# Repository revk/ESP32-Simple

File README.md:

# Simplest code and PCB for ESP32 projects

The code is the simplest build from RevK library, and as such is an ideal base install from which you can OTA any other code. Can also be used as a staged OTA using "otaurl" in the "OTA" namespace in NVS as an automatic OTA when started.

Copyright © 2019-21 Adrian Kennard, Andrews & Arnold Ltd. See LICENCE file for details. GPL 3.0

# Building

Git clone this `--recursive` to get all the submodules, and it should build with just `make`. That actually runs the normal `idf.py` to build. `make menuconfig` can be used to fine tune the settings, but the defaults should be mostly sane. `make flash` should work to program.

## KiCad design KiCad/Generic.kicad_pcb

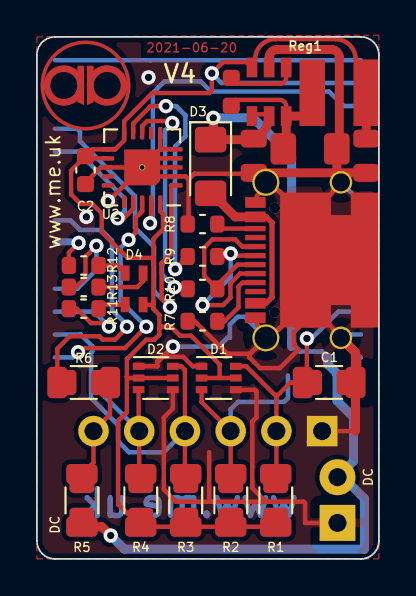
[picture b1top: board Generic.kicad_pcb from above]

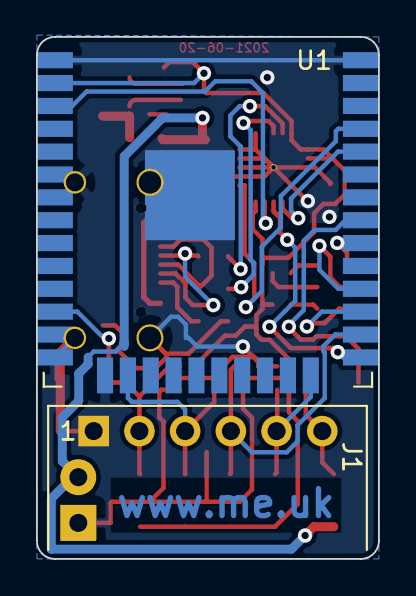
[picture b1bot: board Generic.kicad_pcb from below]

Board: 2 copper layers, 19.0 x 29.0 mm, 26 parts (2 on the bottom side), 26 nets.

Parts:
C1: NF; Pad_1206_0805_NF
C2: 0.1uF; C_0603
D1, D2: BAV99S; SOT-363_SC-70-6
D3: D; D_1206_3216Metric_Pad1.42x1.75mm_HandSolder
D4: LED_RGBA; LED-RGB-1.6x1.6
J1: Connector; Molex_MiniSPOX_H6RA_0.1
J2: USB-C; USC16-TR-Round
J3: PowerIn; DC
Logo1: AA
R1, R2, R3, R4, R5: NF; Pad_1206_0805_NF
R6: 0R; Pad_1206_0805_NF
R7, R8: 5K1; R_0603
R9, R10: 27R; R_0603
R11: 732R; R_0603
R12, R13: 324R; R_0603
Reg1: 3.3V; RegulatorBlock
U1: ESP32-WROOM-32
U2: FT231XQ; QFN-20-1EP_4x4mm_P0.5mm_EP2.5x2.5mm

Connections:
+3V3: C2.1, D1.2, D1.5, D2.2, D2.5, D4.4, R1.1, R2.1, R3.1, R4.1, Reg1.4, U1.2, U2.10, U2.11, U2.12, U2.20
+12V: D3.1, J3.2, R5.1, Reg1.1, Reg1.2
B: R13.2, U1.28
BOOT: U1.25, U2.18
D+: R10.1, U2.8
D-: R9.2, U2.9
EN: U1.3, U2.19
G: R12.2, U1.30
GND: C1.1, C2.2, D1.1, D1.4, D2.1, D2.4, J1.1, J2.A1, J2.A12, J2.B1, J2.B12, J2.S1, J3.1, R7.2, R8.1, Reg1.3, U1.1, U1.6, U1.7, U1.13, U1.14, U1.15, U1.38, U1.39, U2.2, U2.3, U2.4, U2.5, U2.6, U2.13, U2.21
I: U1.34, U2.17
IO1: C1.2, D1.6, J1.2, R1.2, U1.12
IO2: D1.3, J1.3, R2.2, U1.16
IO3: D2.6, J1.4, R3.2, U1.26
IO4: D2.3, J1.5, R4.2, U1.24
IO5: R6.1, U1.31
unnamed: D4.1, R11.1
unnamed: D4.2, R12.1
unnamed: D4.3, R13.1
unnamed: J1.6, R5.2, R6.2
unnamed: J2.A5, R7.1
unnamed: J2.A6, J2.B6, R10.2
unnamed: J2.A7, J2.B7, R9.1
unnamed: J2.B5, R8.2
O: U1.35, U2.1
R: R11.2, U1.27
VBUS: D3.2, J2.A4, J2.A9, J2.B4, J2.B9

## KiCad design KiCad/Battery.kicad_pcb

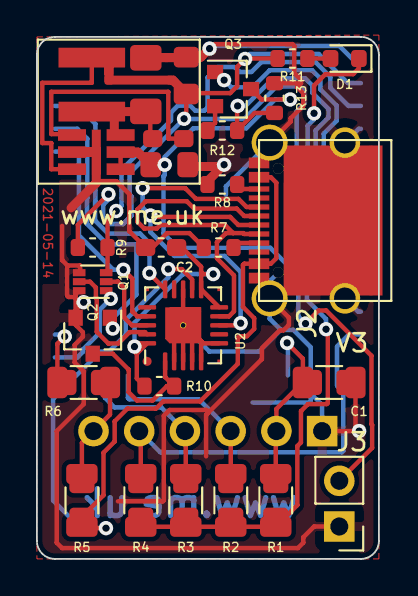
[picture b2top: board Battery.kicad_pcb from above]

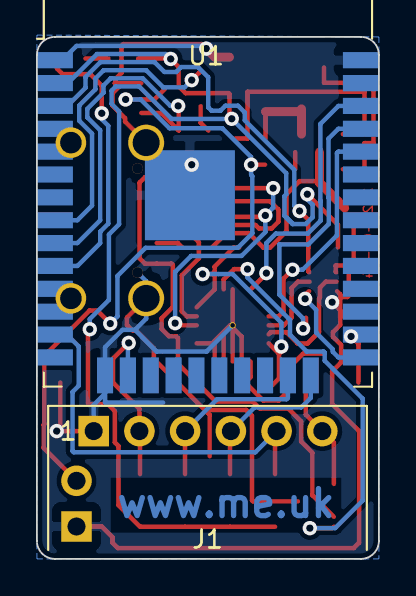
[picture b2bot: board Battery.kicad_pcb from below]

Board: 2 copper layers, 19.0 x 29.0 mm, 25 parts (2 on the bottom side), 28 nets.

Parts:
C1: NF; Pad_1206_0805_NF
C2: 100nF; C_0603_1608Metric_Pad1.08x0.95mm_HandSolder
D1: LED; LED_0603_1608Metric
J1: Connector; Molex_MiniSPOX_H6RA_0.1
J2: USB-C; USC16-TR-Round
J3: DC; PinHeader_1x02_P2.54mm_Vertical
Q1: RN1701; SOT-563
Q2, Q3: BSS169; SOT-23
R1, R2, R3, R4, R5: NF; Pad_1206_0805_NF
R6: 0R; Pad_1206_0805_NF
R7, R8: 5K1; R_0603
R9, R10: 10K; R_0603
R11: 680R; R_0603
R12: 18K; R_0603
R13: 1k; R_0603
Reg1: Regulator; RegulatorBlock
U1: ESP32-WROOM-32
U2: FT231XQ; QFN-20-(hand)-1EP_4x4mm_P0.5mm_EP2.5x2.5mm

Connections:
+3V3: R1.1, R2.1, R3.1, R4.1, R9.2, R11.1, Reg1.4, U1.2
CBUS: U1.36, U2.15
D+: J2.A6, J2.B6, U2.8
D-: J2.A7, J2.B7, U2.9
DC: J3.2, Q3.3, Reg1.1, Reg1.2
EN: Q1.5, U2.19
GND: C1.1, C2.2, J1.1, J2.A1, J2.A12, J2.B1, J2.B12, J2.S1, J3.1, Q1.4, Q1.6, Q2.2, R7.2, R8.1, R13.2, Reg1.3, U1.1, U1.4, U1.5, U1.11, U1.12, U1.15, U1.38, U1.39, U2.2, U2.3, U2.4, U2.5, U2.6, U2.13, U2.21
GPIO0: Q1.2, U2.18
I: U1.34, U2.17
IO1: C1.2, J1.2, R1.2, U1.16
IO2: J1.3, R2.2, U1.23
IO3: J1.4, R3.2, U1.24
IO4: J1.5, R4.2, U1.13
IO5: R6.1, U1.26
unnamed: D1.1, U1.10
unnamed: D1.2, R11.2
unnamed: J1.6, R5.2, R6.2
unnamed: J2.A5, R7.1
unnamed: J2.B5, R8.2
unnamed: Q1.1, U1.25
unnamed: Q1.3, R9.1, U1.3
unnamed: Q2.1, U1.35
unnamed: Q3.1, U1.8
unnamed: Q3.2, R12.1
unnamed: R12.2, R13.1, U1.9
O: Q2.3, R10.2, U2.1
USB3.3: C2.1, R10.1, U2.10, U2.11, U2.20
VBUS: J2.A4, J2.A9, J2.B4, J2.B9, R5.1, U2.12

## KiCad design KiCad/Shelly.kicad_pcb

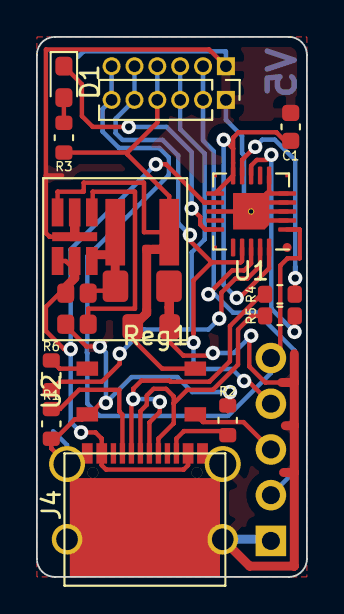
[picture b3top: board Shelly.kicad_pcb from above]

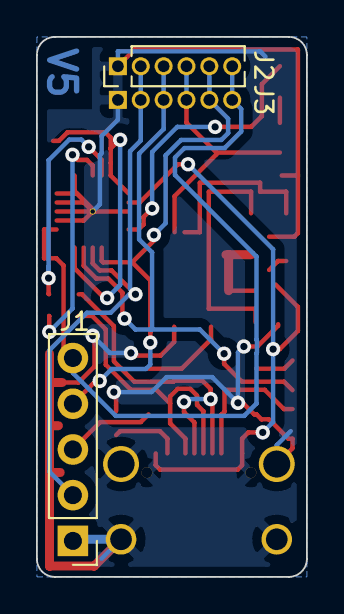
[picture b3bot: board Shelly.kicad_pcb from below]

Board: 2 copper layers, 15.0 x 30.0 mm, 15 parts (2 on the bottom side), 18 nets.

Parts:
C1: 100nF; C_0603
D1: LED; LED_0603_1608Metric_Pad1.05x0.95mm_HandSolder
J1: Shelly 1; PinHeader_1x05_P2.54mm_Vertical
J2: Shelly 2; PinHeader_1x06_P1.27mm_Vertical
J3: Shelly i3; PinHeader_1x06_P1.27mm_Vertical
J4: USB-C; USC16-TR-Round
R1, R2: 5K1; R_0603
R3: 680R; R_0603
R4, R5: 27R; R_0603
R6: 1k; R_0603
Reg1: 3.3V; RegulatorBlock
U1: FT231XQ; QFN-20-(hand)-1EP_4x4mm_P0.5mm_EP2.5x2.5mm
U2: G3VM-61VY3(TR); Special-SOP-4-3.7x4.55

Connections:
+3V3: J2.4, J3.4, R3.1, Reg1.4, U2.4
D+: R5.2, U1.8
D-: R4.2, U1.9
GND: C1.2, J1.1, J2.1, J3.1, J4.A1, J4.A12, J4.B1, J4.B12, J4.S1, R1.2, R2.1, Reg1.3, U1.2, U1.3, U1.4, U1.5, U1.6, U1.13, U1.21, U2.2
GPIO0: J1.2, J2.2, J3.2, U1.18
unnamed: C1.1, U1.10, U1.11, U1.20
unnamed: D1.1, U1.15
unnamed: D1.2, R3.2
unnamed: J1.3, U2.3
unnamed: J4.A5, R1.1
unnamed: J4.A6, J4.B6, R5.1
unnamed: J4.A7, J4.B7, R4.1
unnamed: J4.B5, R2.2
unnamed: R6.1, U2.1
RST: J2.3, J3.3, R6.2, U1.19
RXD: J1.4, J2.5, J3.5, U1.17
TXD: J1.5, J2.6, J3.6, U1.1
VBUS: J4.A4, J4.A9, J4.B4, J4.B9, Reg1.1, Reg1.2, U1.12

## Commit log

2019-08-26 URL is one time use
2019-08-26 Typo
2019-08-27 Copyright
2019-10-27 Library update
2019-10-27 Submodule fix
2019-10-27 Working on it
2019-10-27 Load new 2xOTA partition table on the fly
2019-10-27 Error check
2019-10-27 Error checks
2019-10-27 Better errors
2019-10-28 Simpler
2019-10-28 Added comments
2019-10-28 Comment
2019-10-28 More partition check to main library
2019-12-11 Minor tweak
2021-03-06 Started on Generic PCB
2021-03-06 Looks ready to try
2021-03-06 Clean up silk screen
2021-03-06 Added big cap, but I suspect it will not be enough.
2021-03-06 Tweak silk screen
2021-03-06 LDO added
2021-03-06 Redraw
2021-03-06 Tidy tracks a lot
2021-03-07 Rework, simpler.
2021-03-07 Tidy more...
2021-03-07 Rework to look nicer
2021-03-07 Tidy silk screen
2021-03-08 Added DC header
2021-03-08 Revised library parts
2021-03-08 Tidy up
2021-03-08 Tweak
2021-03-09 Footprint
2021-03-10 Moved GPI0 to CBUS0
2021-03-14 Centred
2021-03-15 PCBCase logic
2021-03-15 Cases
2021-03-15 Depenmdancy
2021-03-16 Edge
2021-03-26 Revised footprint
2021-03-26 Easier soldering
2021-03-27 Much more clearance on regulator pads
2021-03-28 Clearance around FTDI
2021-03-29 Logo
2021-04-11 Option for VBUS connection on SPOX (6)
2021-04-11 V3 board
2021-04-17 Added a Shelly programming board
2021-04-17 Swapped around for easier soldering with heat gun
2021-04-19 V2 Shelly using FT231XQ
2021-04-19 Revised with LED
2021-04-19 RST power control
2021-04-20 Opto isolator
2021-04-20 Tweak tracking slightly
2021-04-21 Corners
2021-04-22 FT231XQ
2021-04-22 Note FT230X
2021-04-22 Fix VBUS via
2021-04-23 Moved resistor
2021-04-23 Notes
2021-04-23 Change to smaller compnent
2021-04-23 Remove note
2021-04-23 Reworked to be smaller (15x30)
2021-04-23 Tidy copper poors around FT231X
2021-04-23 Tidy
2021-04-24 Case
2021-04-27 Values shown
2021-04-29 Shelly case
2021-04-29 Updated cases
2021-05-02 Updated to use new regulator
2021-05-02 Updated case
2021-05-02 New regulator
2021-05-03 Regulator
2021-05-05 Footprint tidy
2021-05-08 Improve fab diagram
2021-05-11 Slight tidy of tracks
2021-05-11 Reworked for ULP pins and ADC pins
2021-05-11 Single sided componets to make solder paste easier
2021-05-11 Multi size pads with no solder past for user fit passives.
2021-05-11 Paste update
2021-05-12 Moved to new project
2021-05-13 Changed to allow USB to be off when DC powered for low power operation...
2021-05-13 Added CBUS pin so you can check the FT231X is on
2021-05-14 Reverted, making separate board for low power
2021-05-14 New battery module - can operator without USB
2021-05-15 Updated to have an LED
2021-05-15 New battery based module (i.e. usb can be totally powered down)
2021-05-15 Regulator update
2021-05-15 Describe PCBs
2021-05-17 Clean up 3D
2021-05-20 Moved battery to BatMon projeect
2021-05-20 Prettier regulator
2021-05-23 Tweak regulater
2021-06-16 Reworked to have diode protection on the first 4 GPIO pins and USB+12V operation via diode
2021-06-17 Better footprint for solder paste
2021-06-18 Reworked wit 27R in USB
2021-06-19 Complete re-layout with RGB LED
2021-06-19 Fix solder paste error
2021-06-19 Tidy GPIO
2021-06-19 Updated drawing
2021-06-20 Tidy for order
2021-06-20 Pad sizes
2021-06-20 The BatMon board basically replaces this.
2022-08-30 Update libraries to build with 4.4.2 and cut down - very simple exmaple now
2026-02-13 submodule
2026-02-15 Codeberg
